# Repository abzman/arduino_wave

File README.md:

arduino_wave
============

self contained arduino and wave shield

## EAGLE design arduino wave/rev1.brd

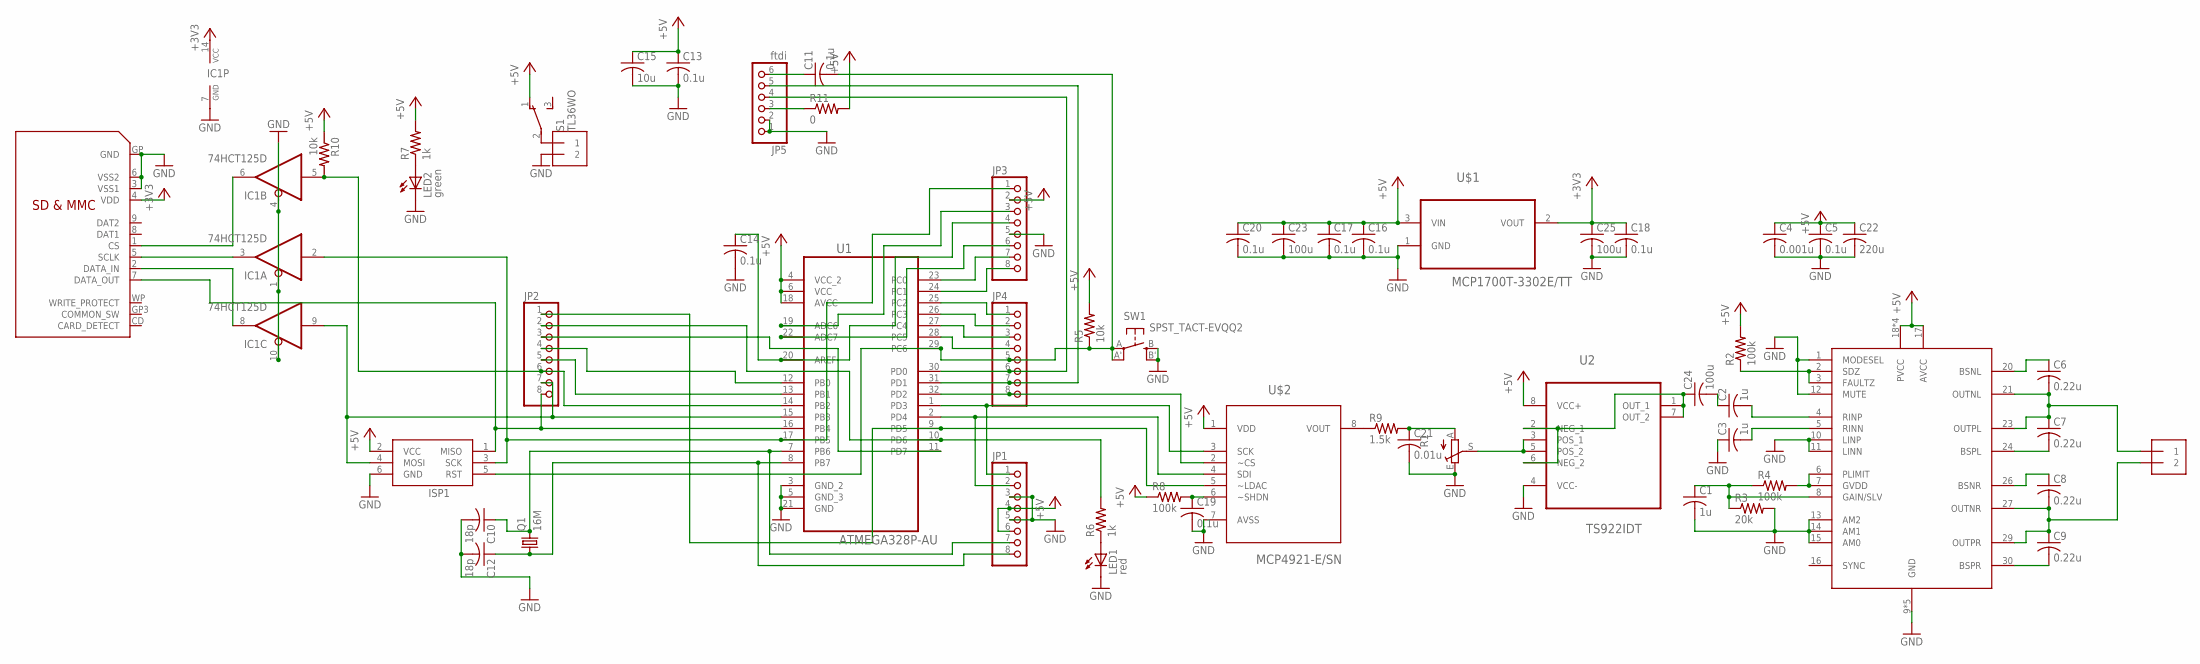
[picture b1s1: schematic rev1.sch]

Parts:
C1, C2, C3: 1u; C0603
C4: 0.001u; C0603
C5, C11, C13, C14, C16, C17, C18, C19, C20: 0.1u; C0603
C6, C7, C8, C9: 0.22u; C0603
C10, C12: 18p; C0603
C15: 10u; C025-050X050
C21: 0.01u; C0603
C22: 220u; C025-060X050
C23, C24, C25: 100u; C025-050X050
IC1: 74HCT125D; SO14
ISP1: AVRISP-6; AVRISP
J1: POWER; 1X2-3.5MM
J2: Speaker; 1X2-3.5MM
JP1, JP2, JP3, JP4: PINHD-1X8BIG; 1X08-BIG
JP5: ftdi; 1X06
LED1: red; LED3MM
LED2: green; LED3MM
Q1: 16M; HC49UP
R1: TRIM_EU-CA9V; CA9V
R2, R4, R8: 100k; R0603
R3: 20k; R0603
R5, R10: 10k; R0603
R6, R7: 1k; R0603
R9: 1.5k; R0603
R11: 0; R0603
S1: TL36WO; TL3XWO
SW1: SPST_TACT-EVQQ2; EVQ-Q2
U1: ATMEGA328P-AU; QFP80P900X900X120-32N
U2: TS922IDT; SOIC127P600X175-8N
U$1: MCP1700T-3302E/TT; SOT95P237X112-3N
U$2: MCP4921-E/SN; SOIC8-N_MC
U$3: SDMMC06132; 06132
U$4: TPA3118D2DAP

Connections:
+3V3: C18.1, C25.1, IC1.14 (VCC), U$1.2 (VOUT), U$3.4 (VDD)
+5V: C4.1, C5.1, C13.1, C15.1, C16.1, C17.1, C20.1, C22.1, C23.1, ISP1.2 (VCC), JP1.4, JP1.6, JP3.2, R2.2, R5.2, R7.2, R8.1, R10.1, R11.2, S1.1 (O), U1.4 (VCC_2), U1.6 (VCC), U1.18 (AVCC), U2.8 (VCC+), U$1.3 (VIN), U$2.1 (VDD), U$4.17 (AVCC), U$4.18 (PVCC), U$4.19 (PVCC), U$4.31 (PVCC), U$4.32 (PVCC)
GND: C1.2, C3.1, C4.2, C5.2, C10.2, C12.2, C13.2, C14.2, C15.2, C16.2, C17.2, C18.2, C19.2, C20.2, C21.2, C22.2, C23.2, C25.2, IC1.1 (OE), IC1.4 (OE), IC1.7 (GND), IC1.10 (OE), ISP1.6 (GND), J1.2, JP1.3, JP1.5, JP3.5, JP5.1, JP5.2, LED1.K (C), LED2.K (C), R1.E, R3.2, SW1.B (S), SW1.B' (S1), U1.3 (GND_2), U1.5 (GND_3), U1.21 (GND), U2.4 (VCC-), U$1.1 (GND), U$2.7 (AVSS), U$3.3 (VSS1), U$3.6 (VSS2), U$3.GP (GND), U$4.1 (MODESEL), U$4.9 (GND), U$4.10 (LINP), U$4.11 (LINN), U$4.12 (MUTE), U$4.13 (AM2), U$4.14 (AM1), U$4.15 (AM0), U$4.22 (GND), U$4.25 (GND), U$4.28 (GND), U$4.33 (GND)
unnamed: C6.1, U$4.20 (BSNL)
unnamed: R2.1, U$4.2 (SDZ), U$4.3 (FAULTZ)
unnamed: R4.2, U$4.6 (PLIMIT), U$4.7 (GVDD)
unnamed: C1.1, R3.1, R4.1, U$4.8 (GAIN/SLV)
unnamed: C6.2, C7.1, J2.1, U$4.21 (OUTNL), U$4.23 (OUTPL)
unnamed: C7.2, U$4.24 (BSPL)
unnamed: C8.1, U$4.26 (BSNR)
unnamed: C3.2, U$4.5 (RINN)
unnamed: C8.2, C9.1, J2.2, U$4.27 (OUTNR), U$4.29 (OUTPR)
unnamed: C9.2, U$4.30 (BSPR)
unnamed: C2.2, U$4.4 (RINP)
unnamed: ISP1.1 (MISO), JP2.8, U1.16 (PB4), U$3.7 (DATA_OUT)
unnamed: C10.1, JP1.7, Q1.2, U1.7 (PB6)
unnamed: JP4.4, U1.28 (PC5)
unnamed: C11.1, JP5.6
unnamed: JP5.3, R11.1
unnamed: C12.1, JP1.8, Q1.1, U1.8 (PB7)
unnamed: LED1.A, R6.1
unnamed: C14.1, JP3.4, U1.20 (AREF)
unnamed: IC1.9 (I), ISP1.4 (MOSI), JP2.7, U1.15 (PB3)
unnamed: JP4.3, U1.27 (PC4)
unnamed: LED2.A, R7.1
unnamed: J1.1, S1.2
unnamed: JP4.7, JP5.5, U1.31 (PD1)
unnamed: JP4.6, JP5.4, U1.30 (PD0)
unnamed: C11.2, ISP1.5 (RST), JP4.5, R5.1, SW1.A, SW1.A' (P1), U1.29 (PC6)
unnamed: JP4.2, U1.26 (PC3)
unnamed: JP4.1, U1.25 (PC2)
unnamed: JP4.8, U1.32 (PD2), U$2.2 (~CS)
unnamed: JP3.8, U1.24 (PC1)
unnamed: JP3.7, U1.23 (PC0)
unnamed: JP3.6, U1.22 (ADC7)
unnamed: JP3.3, U1.19 (ADC6)
unnamed: C24.1, U2.1 (OUT_1), U2.2 (NEG_1), U2.6 (NEG_2), U2.7 (OUT_2)
unnamed: IC1.5 (I), JP2.6, R10.2, U1.14 (PB2)
unnamed: JP2.5, U1.13 (PB1)
unnamed: JP2.4, U1.12 (PB0)
unnamed: JP2.3, U1.11 (PD7)
unnamed: JP2.2, R6.2, U1.10 (PD6)
unnamed: JP2.1, U1.9 (PD5), U$2.5 (~LDAC)
unnamed: R1.S, U2.3 (POS_1), U2.5 (POS_2)
unnamed: C21.1, R1.A, R9.2
unnamed: JP1.1, U1.1 (PD3), U$2.3 (SCK)
unnamed: JP1.2, U1.2 (PD4), U$2.4 (SDI)
unnamed: C2.1, C24.2
unnamed: IC1.3 (O), U$3.5 (SCLK)
unnamed: IC1.8 (O), U$3.2 (DATA_IN)
unnamed: IC1.6 (O), U$3.1 (CS)
unnamed: IC1.2 (I), ISP1.3 (SCK), JP3.1, U1.17 (PB5)
unnamed: C19.1, R8.2, U$2.6 (~SHDN)
unnamed: R9.1, U$2.8 (VOUT)

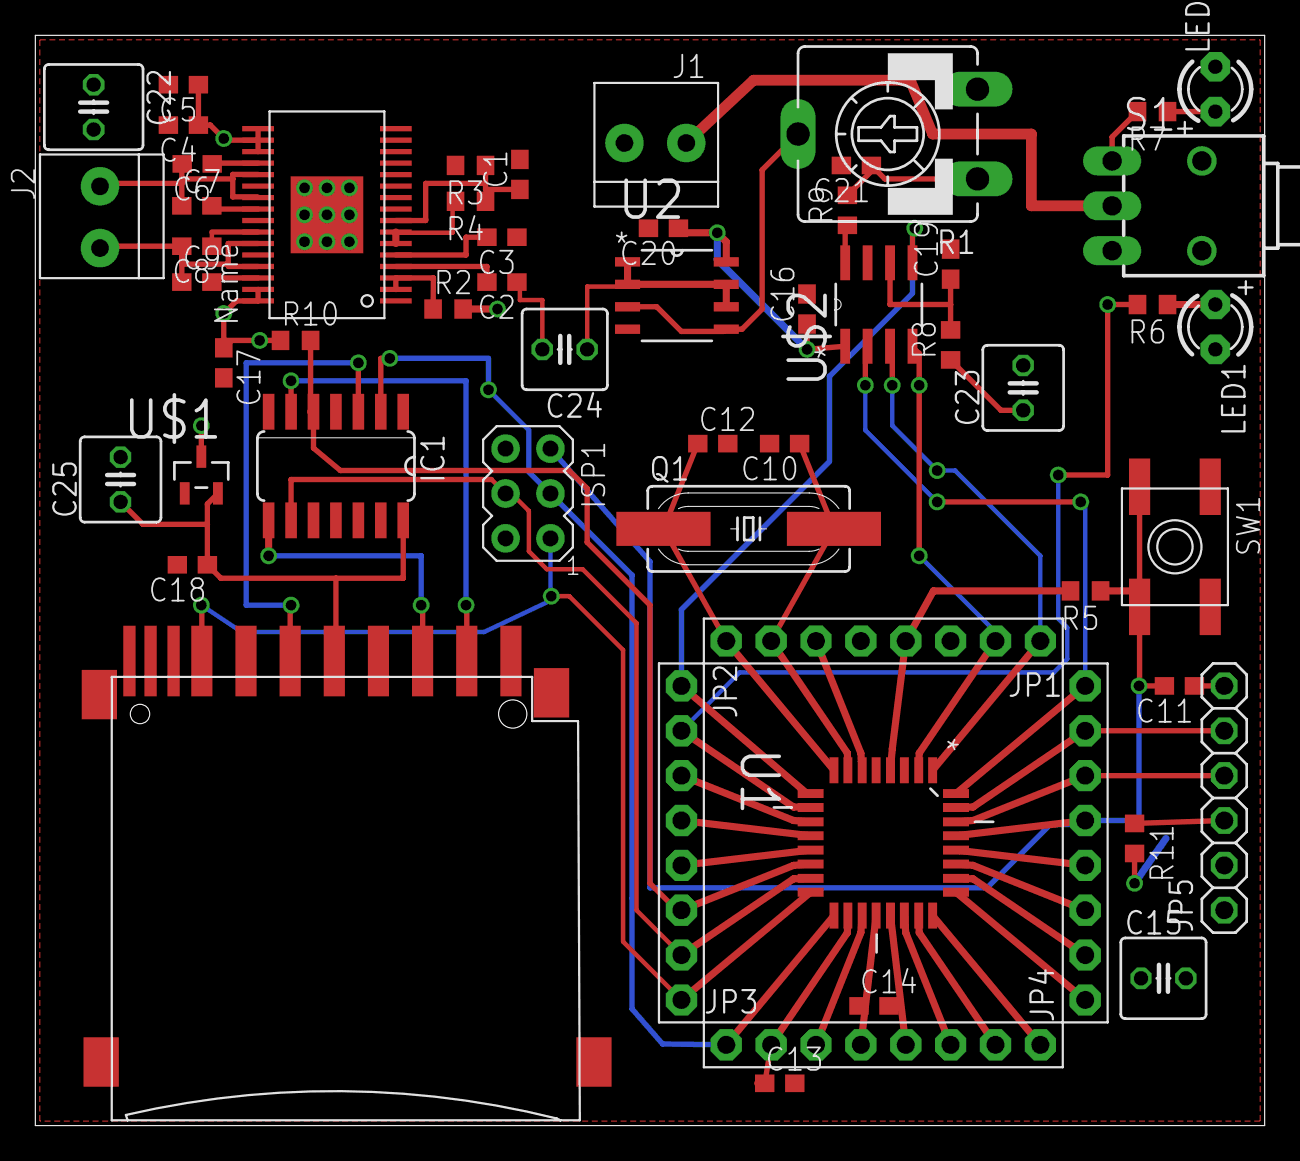
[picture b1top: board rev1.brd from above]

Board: 2 copper layers, 69.6 x 61.7 mm, 56 parts (0 on the bottom side), 54 nets.

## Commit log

2014-06-15 added first files
